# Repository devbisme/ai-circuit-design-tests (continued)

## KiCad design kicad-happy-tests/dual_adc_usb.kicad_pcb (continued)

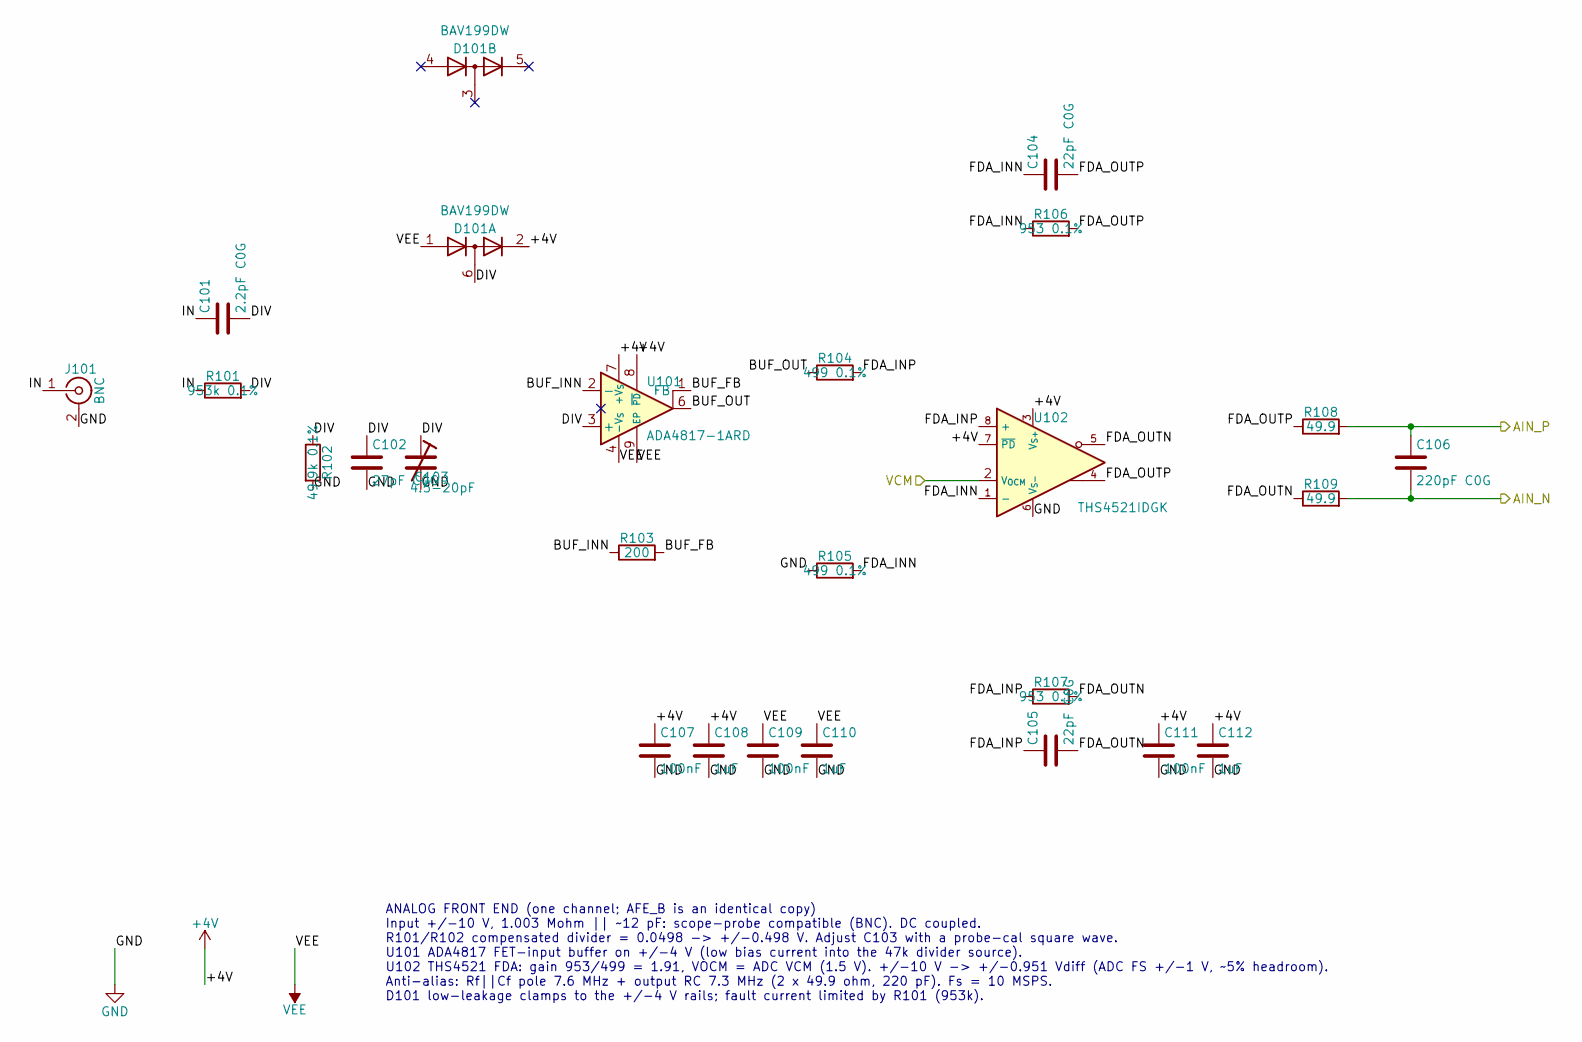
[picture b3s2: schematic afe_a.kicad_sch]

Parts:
C101: 2.2pF C0G; C_0603_1608Metric
C102: 27pF C0G; C_0603_1608Metric
C103: 4.5-20pF; C_Trimmer_Murata_TZB4-A
C104, C105: 22pF C0G; C_0603_1608Metric
C106: 220pF C0G; C_0603_1608Metric
C107, C109, C111: 100nF; C_0402_1005Metric
C108, C110, C112: 1uF; C_0603_1608Metric
D101: BAV199DW; SOT-363_SC-70-6
J101: BNC; BNC_Amphenol_B6252HB-NPP3G-50_Horizontal
R101: 953k 0.1%; R_1206_3216Metric
R102: 49.9k 0.1%; R_0603_1608Metric
R103: 200; R_0603_1608Metric
R104, R105: 499 0.1%; R_0603_1608Metric
R106, R107: 953 0.1%; R_0603_1608Metric
R108, R109: 49.9; R_0603_1608Metric
U101: ADA4817-1ARD; SOIC-8-1EP_3.9x4.9mm_P1.27mm_EP2.29x3mm
U102: THS4521IDGK; VSSOP-8_3x3mm_P0.65mm

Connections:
+4V: C107.1, C108.1, C111.1, C112.1, D101.2 (K2), U101.7 (+V_{S}), U101.8 (~PD), U102.3 (V_{S+}), U102.7 (~PD); also elsewhere on the board
/ADC/AINA_N: C106.2, R109.2; also elsewhere on the board
/ADC/AINA_P: C106.1, R108.2; also elsewhere on the board
/ADC/VCMA: U102.2 (V_{OCM}); also elsewhere on the board
/AFE_A/BUF_FB: R103.2, U101.1 (FB)
/AFE_A/BUF_INN: R103.1, U101.2 (-)
/AFE_A/BUF_OUT: R104.1, U101.6
/AFE_A/DIV: C101.2, C102.1, C103.1, D101.6 (K3A4), R101.2, R102.1, U101.3 (+)
/AFE_A/FDA_INN: C104.1, R105.2, R106.1, U102.1 (-)
/AFE_A/FDA_INP: C105.1, R104.2, R107.1, U102.8 (+)
/AFE_A/FDA_OUTN: C105.2, R107.2, R109.1, U102.5
/AFE_A/FDA_OUTP: C104.2, R106.2, R108.1, U102.4
/AFE_A/IN: C101.1, J101.1 (In), R101.1
GND: C102.2, C103.2, C107.2, C108.2, C109.2, C110.2, C111.2, C112.2, J101.2 (Ext), R102.2, R105.1, U102.6 (V_{S-}); also elsewhere on the board
VEE: C109.1, C110.1, D101.1 (A1), U101.4 (-V_{S}), U101.9 (EP); also elsewhere on the board

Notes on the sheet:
ANALOG FRONT END (one channel; AFE_B is an identical copy) Input +/-10 V, 1.003 Mohm || ~12 pF: scope-probe compatible (BNC). DC coupled. R101/R102 compensated divider = 0.0498 -> +/-0.498 V. Adjust C103 with a probe-cal square wave. U101 ADA4817 FET-input buffer on +/-4 V (low bias current into th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

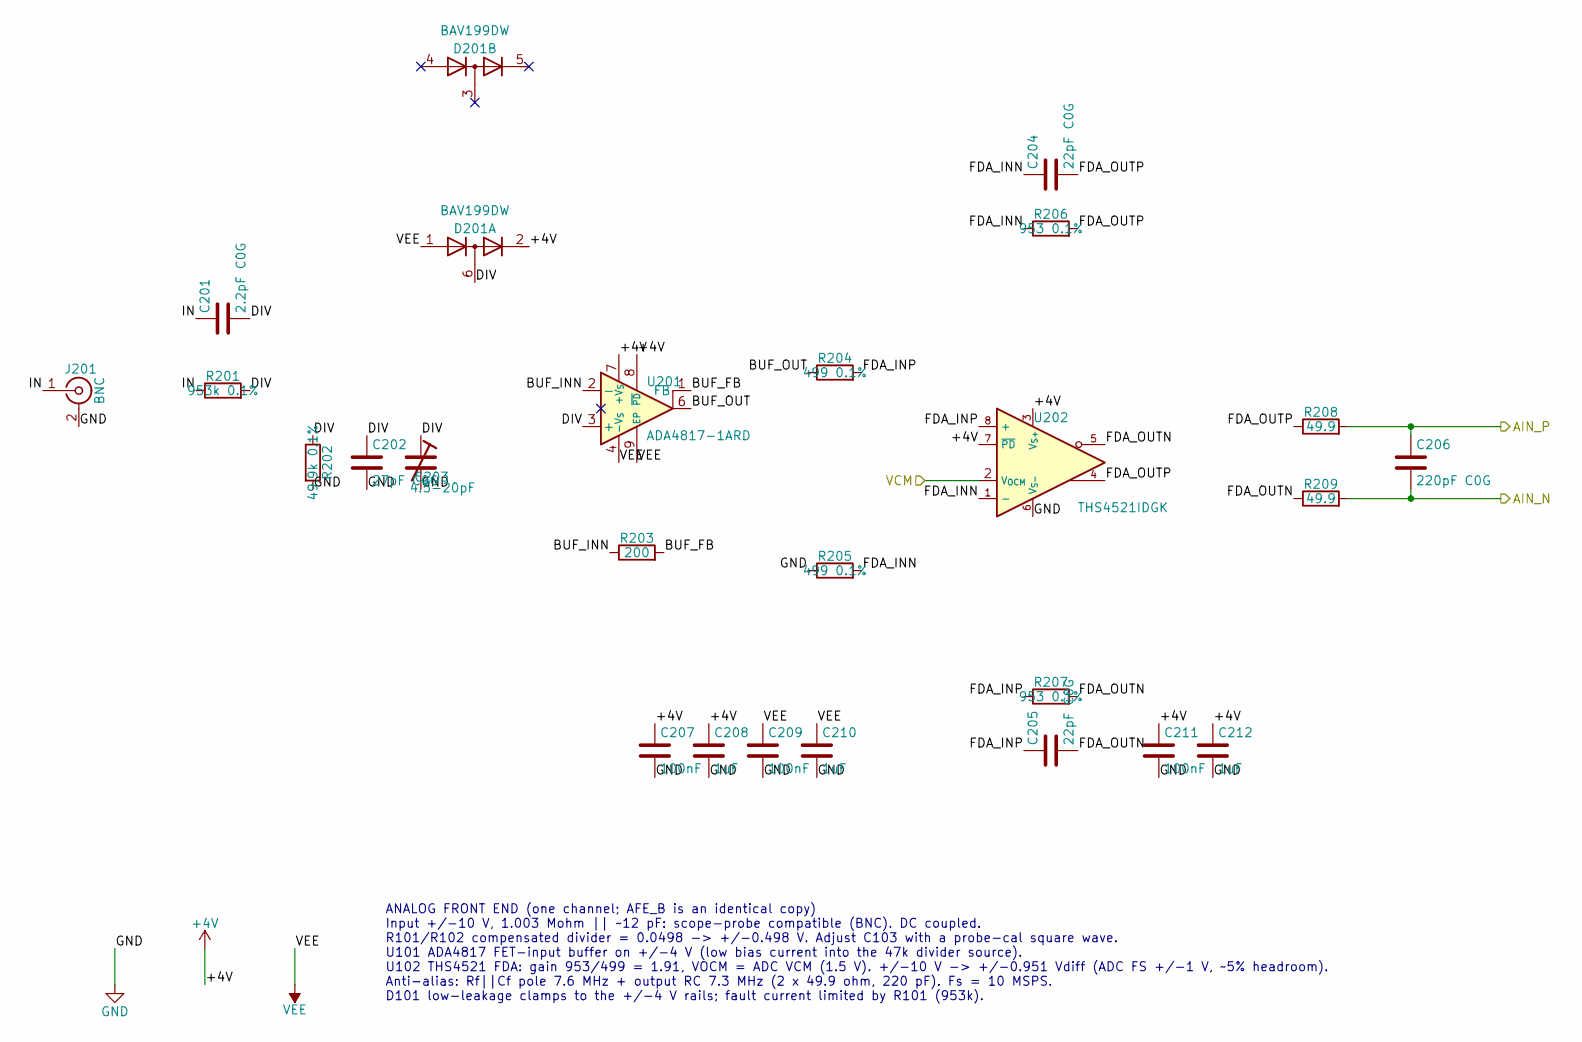
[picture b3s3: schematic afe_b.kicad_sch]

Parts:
C201: 2.2pF C0G; C_0603_1608Metric
C202: 27pF C0G; C_0603_1608Metric
C203: 4.5-20pF; C_Trimmer_Murata_TZB4-A
C204, C205: 22pF C0G; C_0603_1608Metric
C206: 220pF C0G; C_0603_1608Metric
C207, C209, C211: 100nF; C_0402_1005Metric
C208, C210, C212: 1uF; C_0603_1608Metric
D201: BAV199DW; SOT-363_SC-70-6
J201: BNC; BNC_Amphenol_B6252HB-NPP3G-50_Horizontal
R201: 953k 0.1%; R_1206_3216Metric
R202: 49.9k 0.1%; R_0603_1608Metric
R203: 200; R_0603_1608Metric
R204, R205: 499 0.1%; R_0603_1608Metric
R206, R207: 953 0.1%; R_0603_1608Metric
R208, R209: 49.9; R_0603_1608Metric
U201: ADA4817-1ARD; SOIC-8-1EP_3.9x4.9mm_P1.27mm_EP2.29x3mm
U202: THS4521IDGK; VSSOP-8_3x3mm_P0.65mm

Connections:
+4V: C207.1, C208.1, C211.1, C212.1, D201.2 (K2), U201.7 (+V_{S}), U201.8 (~PD), U202.3 (V_{S+}), U202.7 (~PD); also elsewhere on the board
/ADC/AINB_N: C206.2, R209.2; also elsewhere on the board
/ADC/AINB_P: C206.1, R208.2; also elsewhere on the board
/ADC/VCMB: U202.2 (V_{OCM}); also elsewhere on the board
/AFE_B/BUF_FB: R203.2, U201.1 (FB)
/AFE_B/BUF_INN: R203.1, U201.2 (-)
/AFE_B/BUF_OUT: R204.1, U201.6
/AFE_B/DIV: C201.2, C202.1, C203.1, D201.6 (K3A4), R201.2, R202.1, U201.3 (+)
/AFE_B/FDA_INN: C204.1, R205.2, R206.1, U202.1 (-)
/AFE_B/FDA_INP: C205.1, R204.2, R207.1, U202.8 (+)
/AFE_B/FDA_OUTN: C205.2, R207.2, R209.1, U202.5
/AFE_B/FDA_OUTP: C204.2, R206.2, R208.1, U202.4
/AFE_B/IN: C201.1, J201.1 (In), R201.1
GND: C202.2, C203.2, C207.2, C208.2, C209.2, C210.2, C211.2, C212.2, J201.2 (Ext), R202.2, R205.1, U202.6 (V_{S-}); also elsewhere on the board
VEE: C209.1, C210.1, D201.1 (A1), U201.4 (-V_{S}), U201.9 (EP); also elsewhere on the board

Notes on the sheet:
ANALOG FRONT END (one channel; AFE_B is an identical copy) Input +/-10 V, 1.003 Mohm || ~12 pF: scope-probe compatible (BNC). DC coupled. R101/R102 compensated divider = 0.0498 -> +/-0.498 V. Adjust C103 with a probe-cal square wave. U101 ADA4817 FET-input buffer on +/-4 V (low bias current into th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

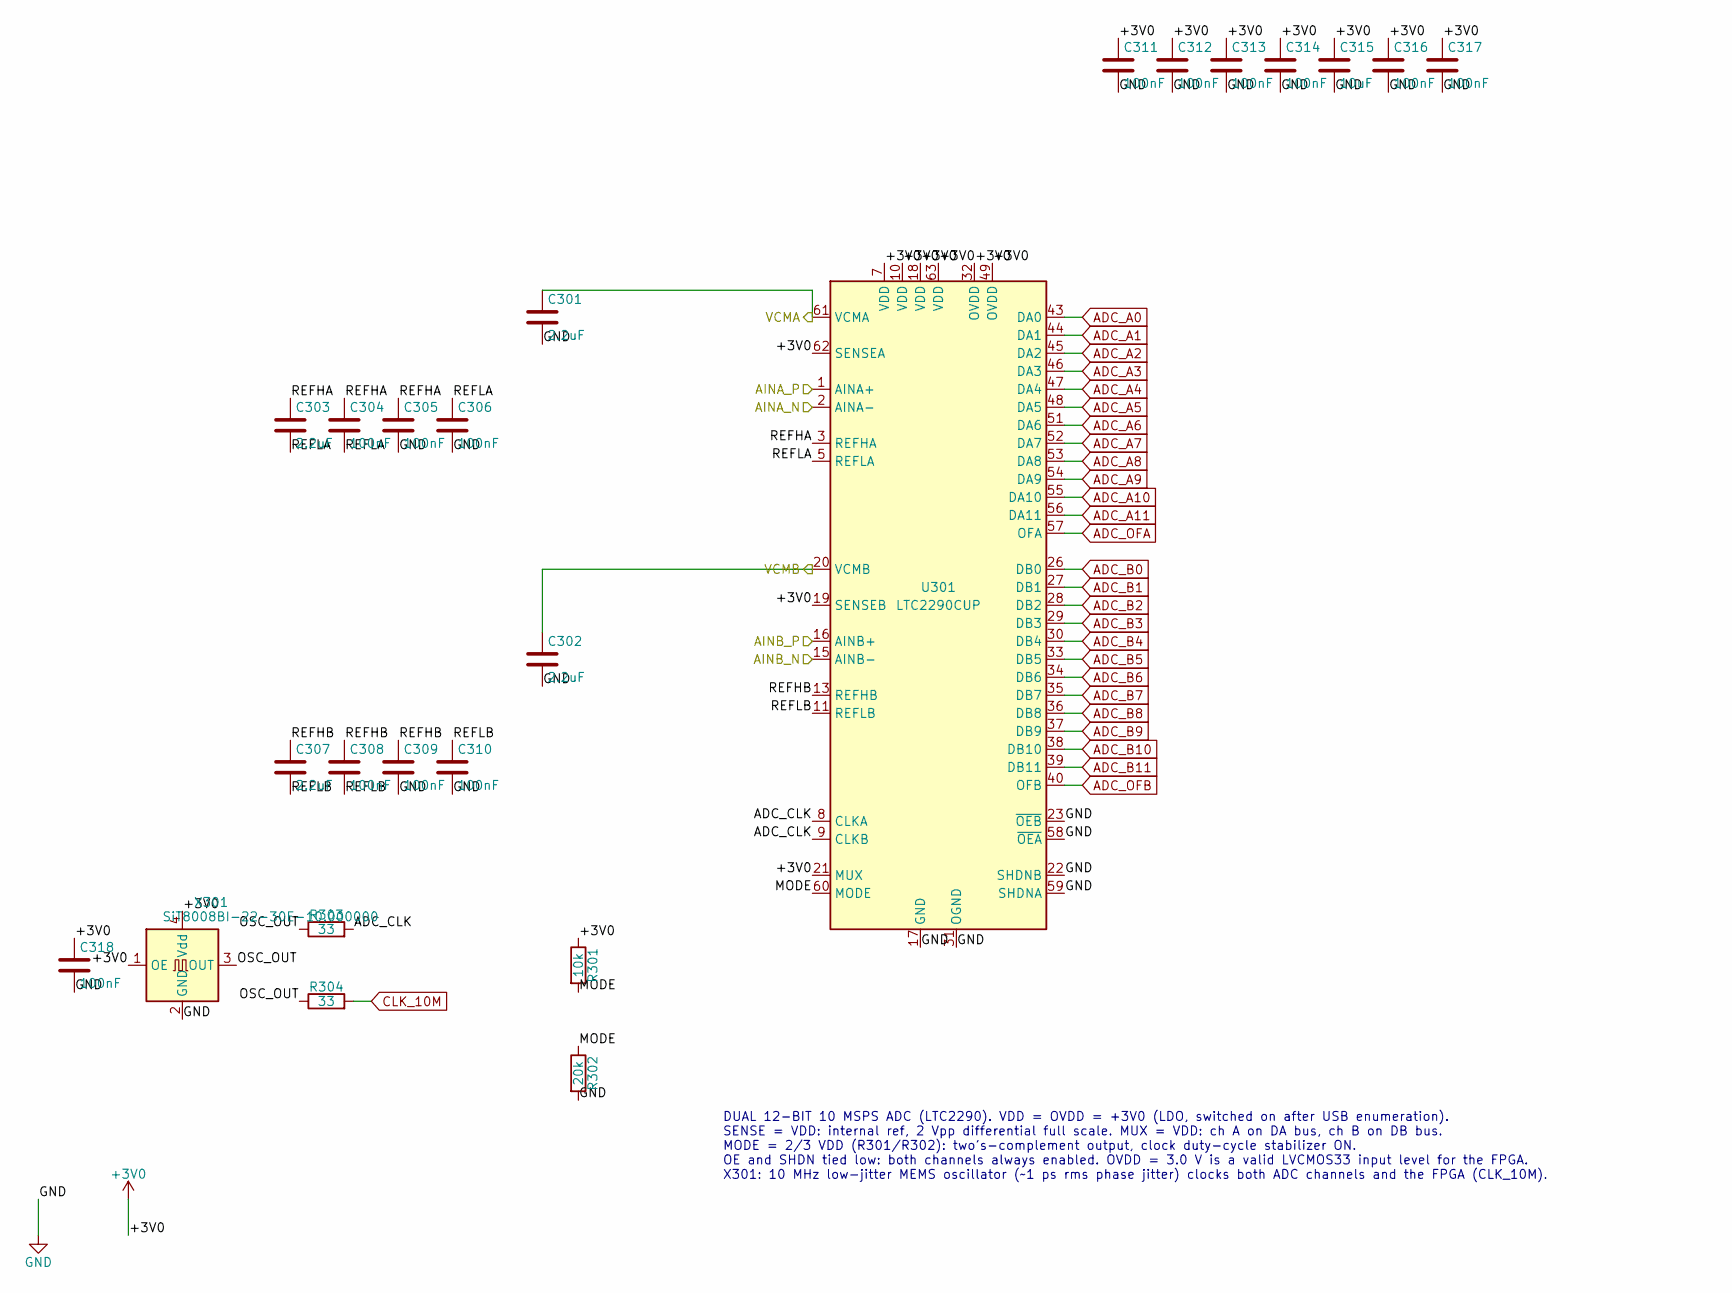
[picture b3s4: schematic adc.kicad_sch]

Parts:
C301, C302, C303, C307: 2.2uF; C_0603_1608Metric
C304, C305, C306, C308, C309, C310, C311, C312, C313, C314, C316, C317, C318: 100nF; C_0402_1005Metric
C315: 10uF; C_0805_2012Metric
R301: 10k; R_0402_1005Metric
R302: 20k; R_0402_1005Metric
R303, R304: 33; R_0402_1005Metric
U301: LTC2290CUP; QFN-64-1EP_9x9mm_P0.5mm_EP7.15x7.15mm
X301: SiT8008BI-22-30E-10.000000; Oscillator_SMD_SiT_PQFN-4Pin_3.2x2.5mm

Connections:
+3V0: C311.1, C312.1, C313.1, C314.1, C315.1, C316.1, C317.1, C318.1, R301.1, U301.7 (VDD), U301.10 (VDD), U301.18 (VDD), U301.19 (SENSEB), U301.21 (MUX), U301.32 (OVDD), U301.49 (OVDD), U301.62 (SENSEA), U301.63 (VDD), X301.1 (OE), X301.4 (Vdd); also elsewhere on the board
/ADC/ADC_CLK: R303.2, U301.8 (CLKA), U301.9 (CLKB)
/ADC/AINA_N: U301.2 (AINA-); also elsewhere on the board
/ADC/AINA_P: U301.1 (AINA+); also elsewhere on the board
/ADC/AINB_N: U301.15 (AINB-); also elsewhere on the board
/ADC/AINB_P: U301.16 (AINB+); also elsewhere on the board
/ADC/MODE: R301.2, R302.1, U301.60 (MODE)
/ADC/OSC_OUT: R303.1, R304.1, X301.3 (OUT)
/ADC/REFHA: C303.1, C304.1, C305.1, U301.3 (REFHA), U301.4 (REFHA)
/ADC/REFHB: C307.1, C308.1, C309.1, U301.13 (REFHB), U301.14 (REFHB)
/ADC/REFLA: C303.2, C304.2, C306.1, U301.5 (REFLA), U301.6 (REFLA)
/ADC/REFLB: C307.2, C308.2, C310.1, U301.11 (REFLB), U301.12 (REFLB)
/ADC/VCMA: C301.1, U301.61 (VCMA); also elsewhere on the board
/ADC/VCMB: C302.1, U301.20 (VCMB); also elsewhere on the board
ADC_A0: U301.43 (DA0); also elsewhere on the board
ADC_A1: U301.44 (DA1); also elsewhere on the board
ADC_A2: U301.45 (DA2); also elsewhere on the board
ADC_A3: U301.46 (DA3); also elsewhere on the board
ADC_A4: U301.47 (DA4); also elsewhere on the board
ADC_A5: U301.48 (DA5); also elsewhere on the board
ADC_A6: U301.51 (DA6); also elsewhere on the board
ADC_A7: U301.52 (DA7); also elsewhere on the board
ADC_A8: U301.53 (DA8); also elsewhere on the board
ADC_A9: U301.54 (DA9); also elsewhere on the board
ADC_A10: U301.55 (DA10); also elsewhere on the board
ADC_A11: U301.56 (DA11); also elsewhere on the board
ADC_B0: U301.26 (DB0); also elsewhere on the board
ADC_B1: U301.27 (DB1); also elsewhere on the board
ADC_B2: U301.28 (DB2); also elsewhere on the board
ADC_B3: U301.29 (DB3); also elsewhere on the board
ADC_B4: U301.30 (DB4); also elsewhere on the board
ADC_B5: U301.33 (DB5); also elsewhere on the board
ADC_B6: U301.34 (DB6); also elsewhere on the board
ADC_B7: U301.35 (DB7); also elsewhere on the board
ADC_B8: U301.36 (DB8); also elsewhere on the board
ADC_B9: U301.37 (DB9); also elsewhere on the board
ADC_B10: U301.38 (DB10); also elsewhere on the board
ADC_B11: U301.39 (DB11); also elsewhere on the board
ADC_OFA: U301.57 (OFA); also elsewhere on the board
ADC_OFB: U301.40 (OFB); also elsewhere on the board
CLK_10M: R304.2; also elsewhere on the board
GND: C301.2, C302.2, C305.2, C306.2, C309.2, C310.2, C311.2, C312.2, C313.2, C314.2, C315.2, C316.2, C317.2, C318.2, R302.2, U301.17 (GND), U301.22 (SHDNB), U301.23 (~OEB), U301.31 (OGND), U301.50 (OGND), U301.58 (~OEA), U301.59 (SHDNA), U301.64 (GND), U301.65 (GND), X301.2 (GND); also elsewhere on the board

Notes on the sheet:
DUAL 12-BIT 10 MSPS ADC (LTC2290). VDD = OVDD = +3V0 (LDO, switched on after USB enumeration). SENSE = VDD: internal ref, 2 Vpp differential full scale. MUX = VDD: ch A on DA bus, ch B on DB bus. MODE = 2/3 VDD (R301/R302): two's-complement output, clock duty-cycle stabilizer ON. OE and SHDN tied l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

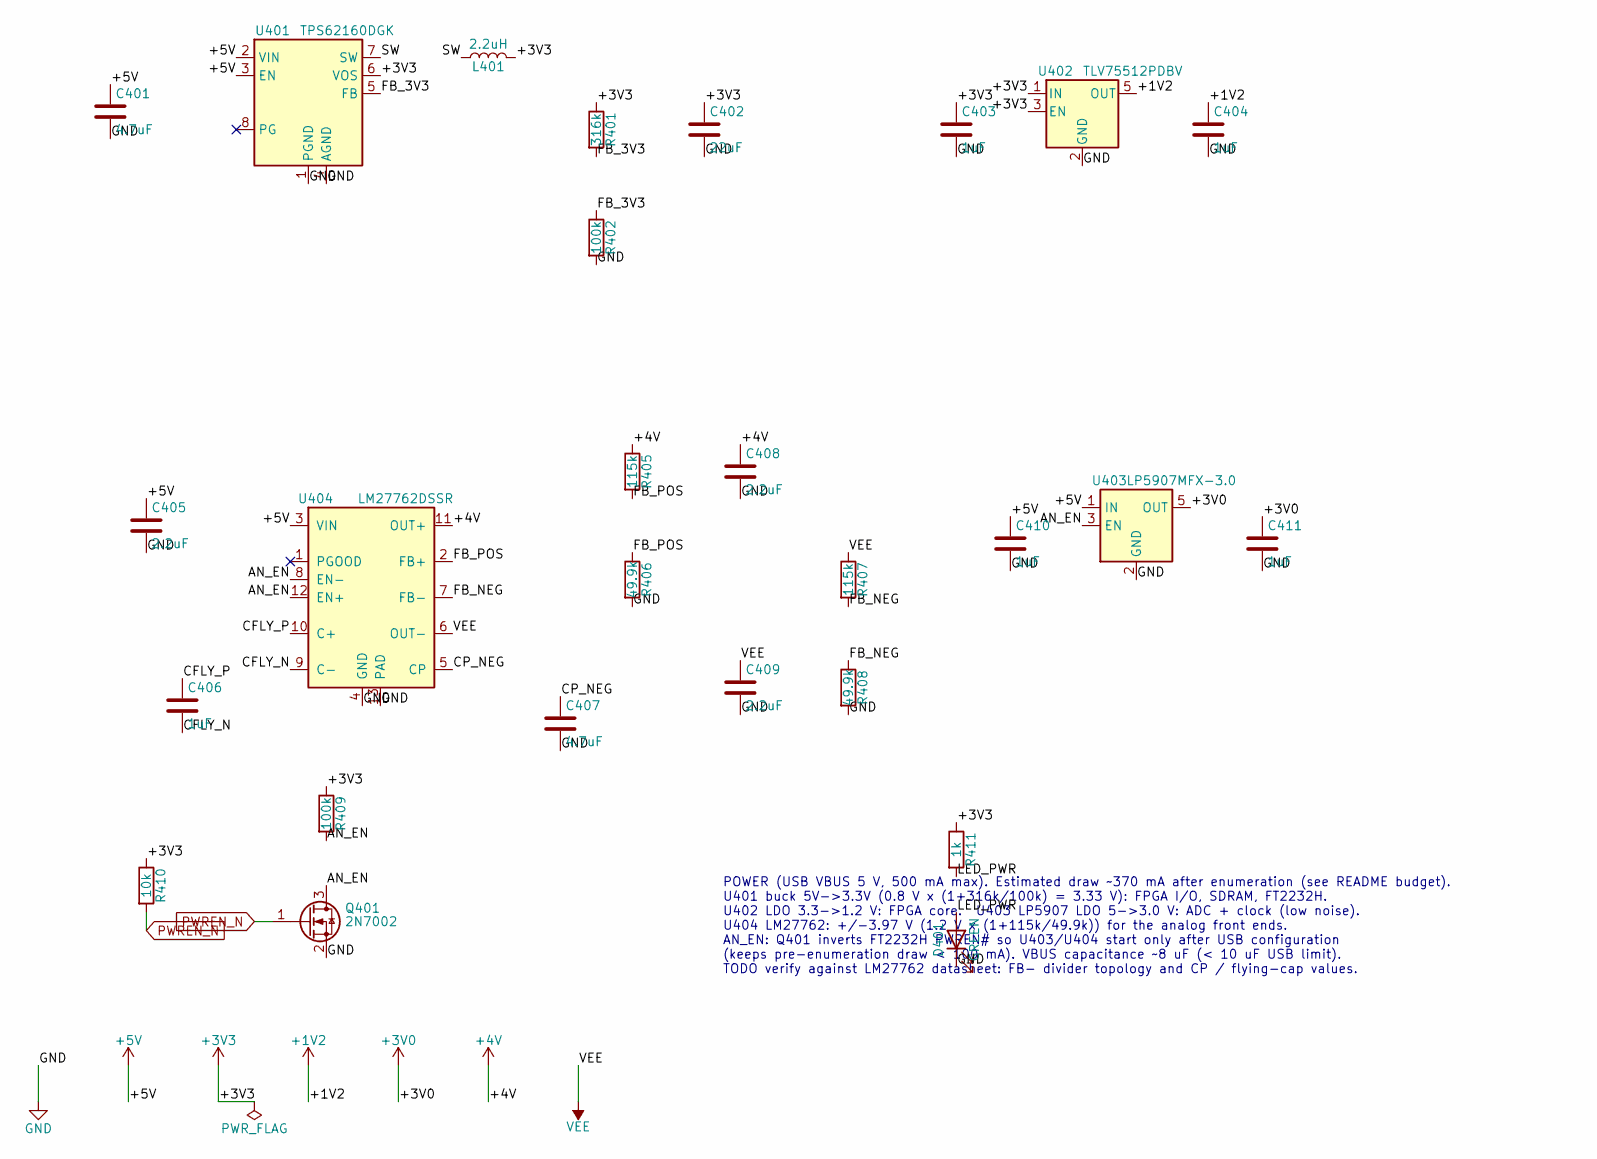
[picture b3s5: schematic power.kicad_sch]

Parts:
C401: 4.7uF; C_0805_2012Metric
C402: 22uF; C_0805_2012Metric
C403, C404, C406, C410, C411: 1uF; C_0603_1608Metric
C405, C408, C409: 2.2uF; C_0603_1608Metric
C407: 4.7uF; C_0603_1608Metric
D401: GREEN; LED_0603_1608Metric
L401: 2.2uH; L_Taiyo-Yuden_NR-30xx
Q401: 2N7002; SOT-23
R401: 316k; R_0402_1005Metric
R402, R409: 100k; R_0402_1005Metric
R405, R407: 115k; R_0402_1005Metric
R406, R408: 49.9k; R_0402_1005Metric
R410: 10k; R_0402_1005Metric
R411: 1k; R_0402_1005Metric
U401: TPS62160DGK; MSOP-8_3x3mm_P0.65mm
U402: TLV75512PDBV; SOT-23-5
U403: LP5907MFX-3.0; SOT-23-5
U404: LM27762DSSR; WSON-12-1EP_3x2mm_P0.5mm_EP1x2.65_ThermalVias

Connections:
+1V2: C404.1, U402.5 (OUT); also elsewhere on the board
+3V0: C411.1, U403.5 (OUT); also elsewhere on the board
+3V3: C402.1, C403.1, L401.2, R401.1, R409.1, R410.1, R411.1, U401.6 (VOS), U402.1 (IN), U402.3 (EN); also elsewhere on the board
+4V: C408.1, R405.1, U404.11 (OUT+); also elsewhere on the board
+5V: C401.1, C405.1, C410.1, U401.2 (VIN), U401.3 (EN), U403.1 (IN), U404.3 (VIN); also elsewhere on the board
/Power/AN_EN: Q401.3 (D), R409.2, U403.3 (EN), U404.8 (EN-), U404.12 (EN+)
/Power/CFLY_N: C406.2, U404.9 (C-)
/Power/CFLY_P: C406.1, U404.10 (C+)
/Power/CP_NEG: C407.1, U404.5 (CP)
/Power/FB_3V3: R401.2, R402.1, U401.5 (FB)
/Power/FB_NEG: R407.2, R408.1, U404.7 (FB-)
/Power/FB_POS: R405.2, R406.1, U404.2 (FB+)
/Power/LED_PWR: D401.2 (A), R411.2
/Power/SW: L401.1, U401.7 (SW)
GND: C401.2, C402.2, C403.2, C404.2, C405.2, C407.2, C408.2, C409.2, C410.2, C411.2, D401.1 (K), Q401.2 (S), R402.2, R406.2, R408.2, U401.1 (PGND), U401.4 (AGND), U402.2 (GND), U403.2 (GND), U404.4 (GND), U404.13 (PAD); also elsewhere on the board
PWREN_N: Q401.1 (G), R410.2; also elsewhere on the board
VEE: C409.1, R407.1, U404.6 (OUT-); also elsewhere on the board

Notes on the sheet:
POWER (USB VBUS 5 V, 500 mA max). Estimated draw ~370 mA after enumeration (see README budget). U401 buck 5V->3.3V (0.8 V x (1+316k/100k) = 3.33 V): FPGA I/O, SDRAM, FT2232H. U402 LDO 3.3->1.2 V: FPGA core. U403 LP5907 LDO 5->3.0 V: ADC + clock (low noise). U404 LM27762: +/-3.97 V (1.2 V x (1+115k/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

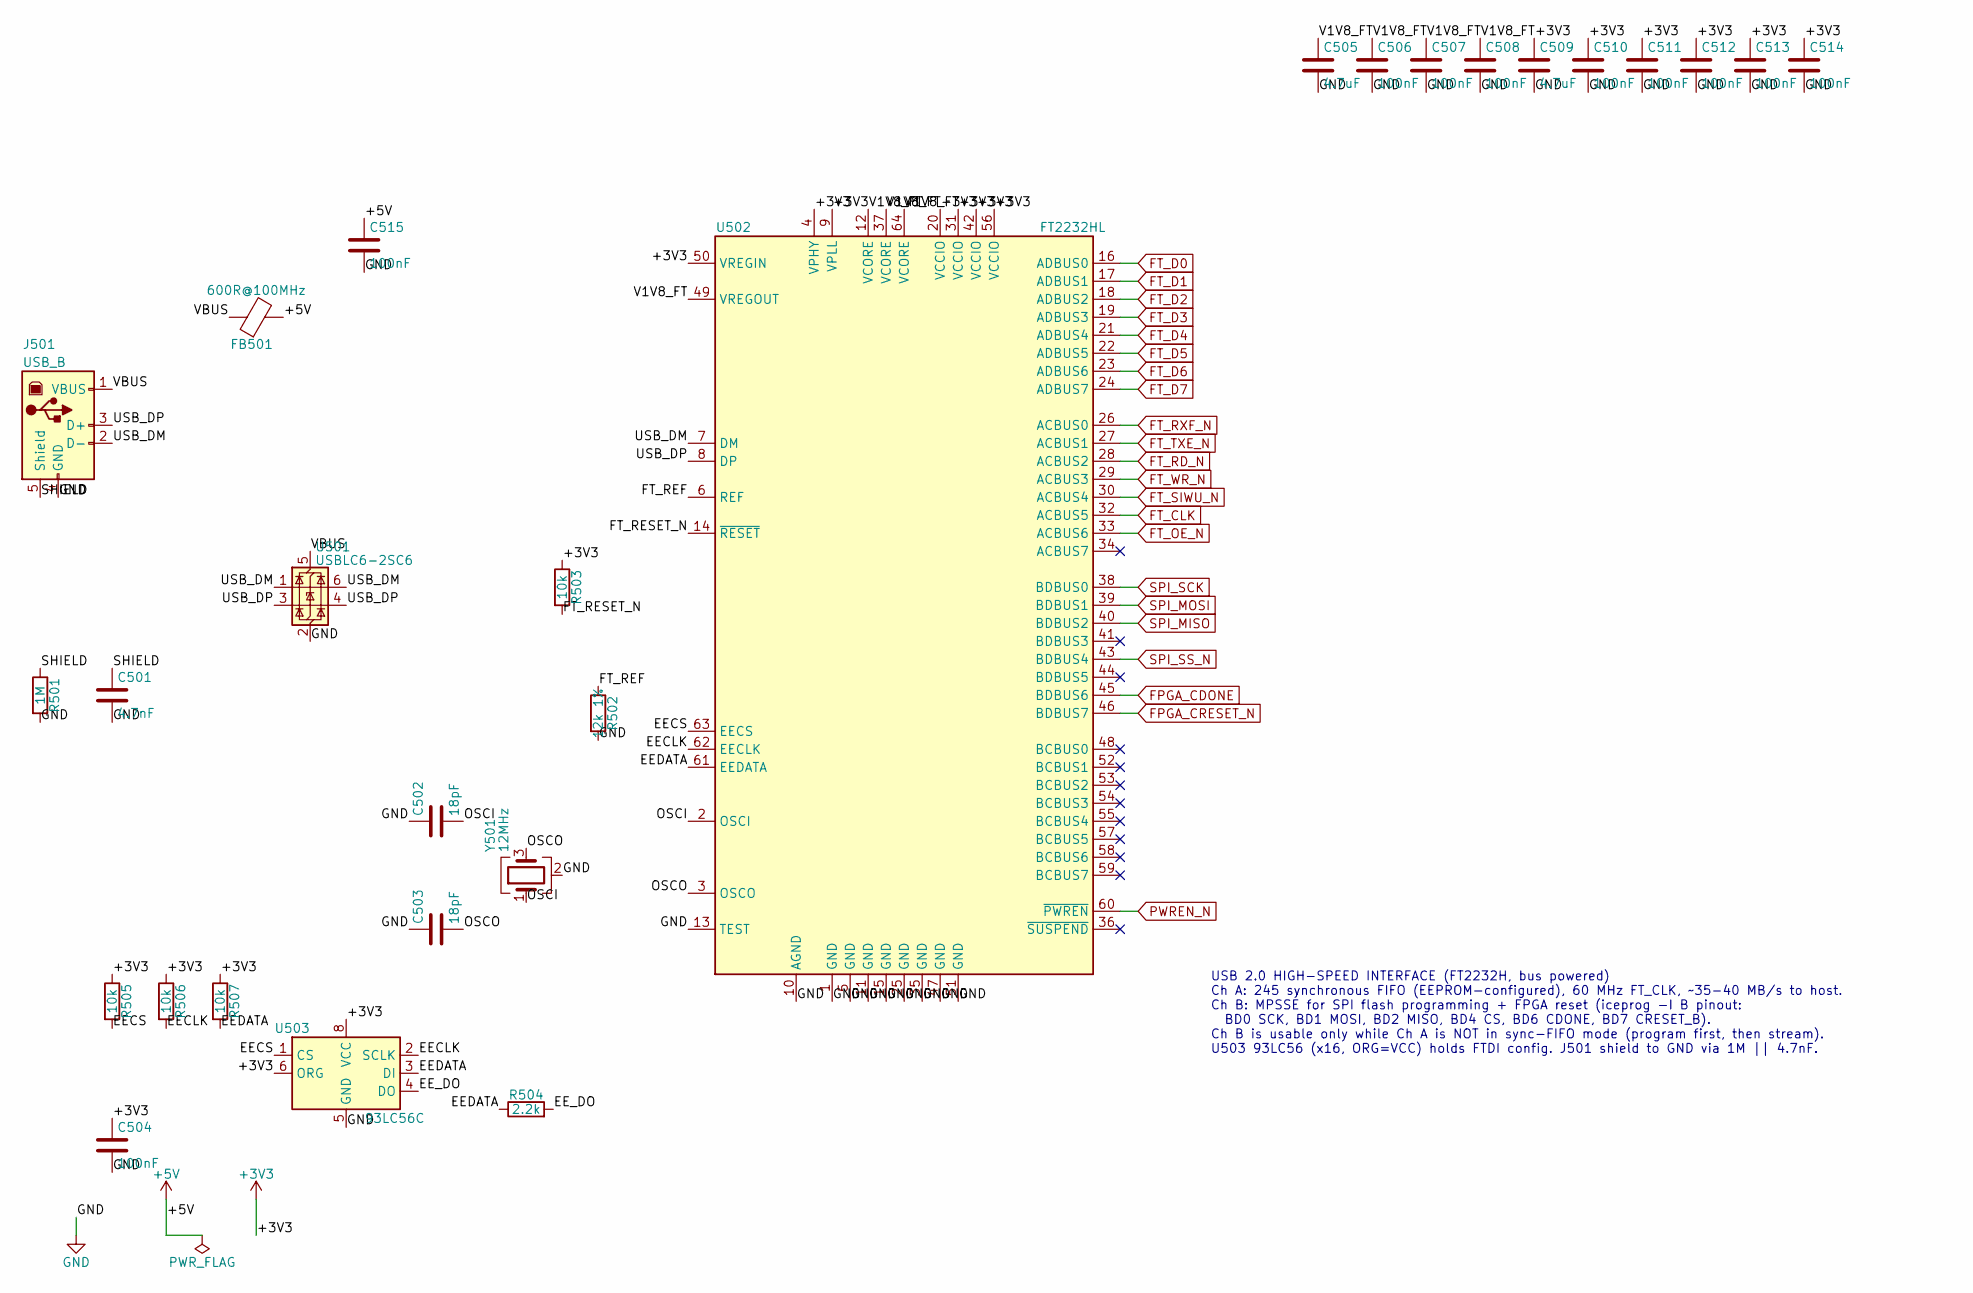
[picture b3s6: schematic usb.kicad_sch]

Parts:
C501: 4.7nF; C_0603_1608Metric
C502, C503: 18pF; C_0402_1005Metric
C504, C506, C507, C508, C510, C511, C512, C513, C514, C515: 100nF; C_0402_1005Metric
C505, C509: 4.7uF; C_0603_1608Metric
FB501: 600R@100MHz; L_0805_2012Metric
J501: USB_B; USB_B_OST_USB-B1HSxx_Horizontal
R501: 1M; R_0603_1608Metric
R502: 12k 1%; R_0402_1005Metric
R503, R505, R506, R507: 10k; R_0402_1005Metric
R504: 2.2k; R_0402_1005Metric
U501: USBLC6-2SC6; SOT-23-6
U502: FT2232HL; LQFP-64_10x10mm_P0.5mm
U503: 93LC56C; SOIC-8_3.9x4.9mm_P1.27mm
Y501: 12MHz; Crystal_SMD_3225-4Pin_3.2x2.5mm

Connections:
+3V3: C504.1, C509.1, C510.1, C511.1, C512.1, C513.1, C514.1, R503.1, R505.1, R506.1, R507.1, U502.4 (VPHY), U502.9 (VPLL), U502.20 (VCCIO), U502.31 (VCCIO), U502.42 (VCCIO), U502.50 (VREGIN), U502.56 (VCCIO), U503.6 (ORG), U503.8 (VCC); also elsewhere on the board
+5V: C515.1, FB501.2; also elsewhere on the board
/USB/EECLK: R506.2, U502.62 (EECLK), U503.2 (SCLK)
/USB/EECS: R505.2, U502.63 (EECS), U503.1 (CS)
/USB/EEDATA: R504.1, R507.2, U502.61 (EEDATA), U503.3 (DI)
/USB/EE_DO: R504.2, U503.4 (DO)
/USB/FT_REF: R502.1, U502.6 (REF)
/USB/FT_RESET_N: R503.2, U502.14 (~RESET)
/USB/OSCI: C502.2, U502.2 (OSCI), Y501.1
/USB/OSCO: C503.2, U502.3 (OSCO), Y501.3
/USB/SHIELD: C501.1, J501.5 (Shield), R501.1
/USB/USB_DM: J501.2 (D-), U501.1 (I/O1), U501.6 (I/O1), U502.7 (DM)
/USB/USB_DP: J501.3 (D+), U501.3 (I/O2), U501.4 (I/O2), U502.8 (DP)
/USB/V1V8_FT: C505.1, C506.1, C507.1, C508.1, U502.12 (VCORE), U502.37 (VCORE), U502.49 (VREGOUT), U502.64 (VCORE)
/USB/VBUS: FB501.1, J501.1 (VBUS), U501.5 (VBUS)
FPGA_CDONE: U502.45 (BDBUS6); also elsewhere on the board
FPGA_CRESET_N: U502.46 (BDBUS7); also elsewhere on the board
FT_CLK: U502.32 (ACBUS5); also elsewhere on the board
FT_D0: U502.16 (ADBUS0); also elsewhere on the board
FT_D1: U502.17 (ADBUS1); also elsewhere on the board
FT_D2: U502.18 (ADBUS2); also elsewhere on the board
FT_D3: U502.19 (ADBUS3); also elsewhere on the board
FT_D4: U502.21 (ADBUS4); also elsewhere on the board
FT_D5: U502.22 (ADBUS5); also elsewhere on the board
FT_D6: U502.23 (ADBUS6); also elsewhere on the board
FT_D7: U502.24 (ADBUS7); also elsewhere on the board
FT_OE_N: U502.33 (ACBUS6); also elsewhere on the board
FT_RD_N: U502.28 (ACBUS2); also elsewhere on the board
FT_RXF_N: U502.26 (ACBUS0); also elsewhere on the board
FT_SIWU_N: U502.30 (ACBUS4); also elsewhere on the board
FT_TXE_N: U502.27 (ACBUS1); also elsewhere on the board
FT_WR_N: U502.29 (ACBUS3); also elsewhere on the board
GND: C501.2, C502.1, C503.1, C504.2, C505.2, C506.2, C507.2, C508.2, C509.2, C510.2, C511.2, C512.2, C513.2, C514.2, C515.2, J501.4 (GND), R501.2, R502.2, U501.2 (GND), U502.1 (GND), U502.5 (GND), U502.10 (AGND), U502.11 (GND), U502.13 (TEST), U502.15 (GND), U502.25 (GND), U502.35 (GND), U502.47 (GND), U502.51 (GND), U503.5 (GND), Y501.2 (G), Y501.4 (G); also elsewhere on the board
PWREN_N: U502.60 (~PWREN); also elsewhere on the board
SPI_MISO: U502.40 (BDBUS2); also elsewhere on the board
SPI_MOSI: U502.39 (BDBUS1); also elsewhere on the board
SPI_SCK: U502.38 (BDBUS0); also elsewhere on the board
SPI_SS_N: U502.43 (BDBUS4); also elsewhere on the board

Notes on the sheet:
USB 2.0 HIGH-SPEED INTERFACE (FT2232H, bus powered) Ch A: 245 synchronous FIFO (EEPROM-configured), 60 MHz FT_CLK, ~35-40 MB/s to host. Ch B: MPSSE for SPI flash programming + FPGA reset (iceprog -I B pinout: BD0 SCK, BD1 MOSI, BD2 MISO, BD4 CS, BD6 CDONE, BD7 CRESET_B). Ch B is usable only while C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
